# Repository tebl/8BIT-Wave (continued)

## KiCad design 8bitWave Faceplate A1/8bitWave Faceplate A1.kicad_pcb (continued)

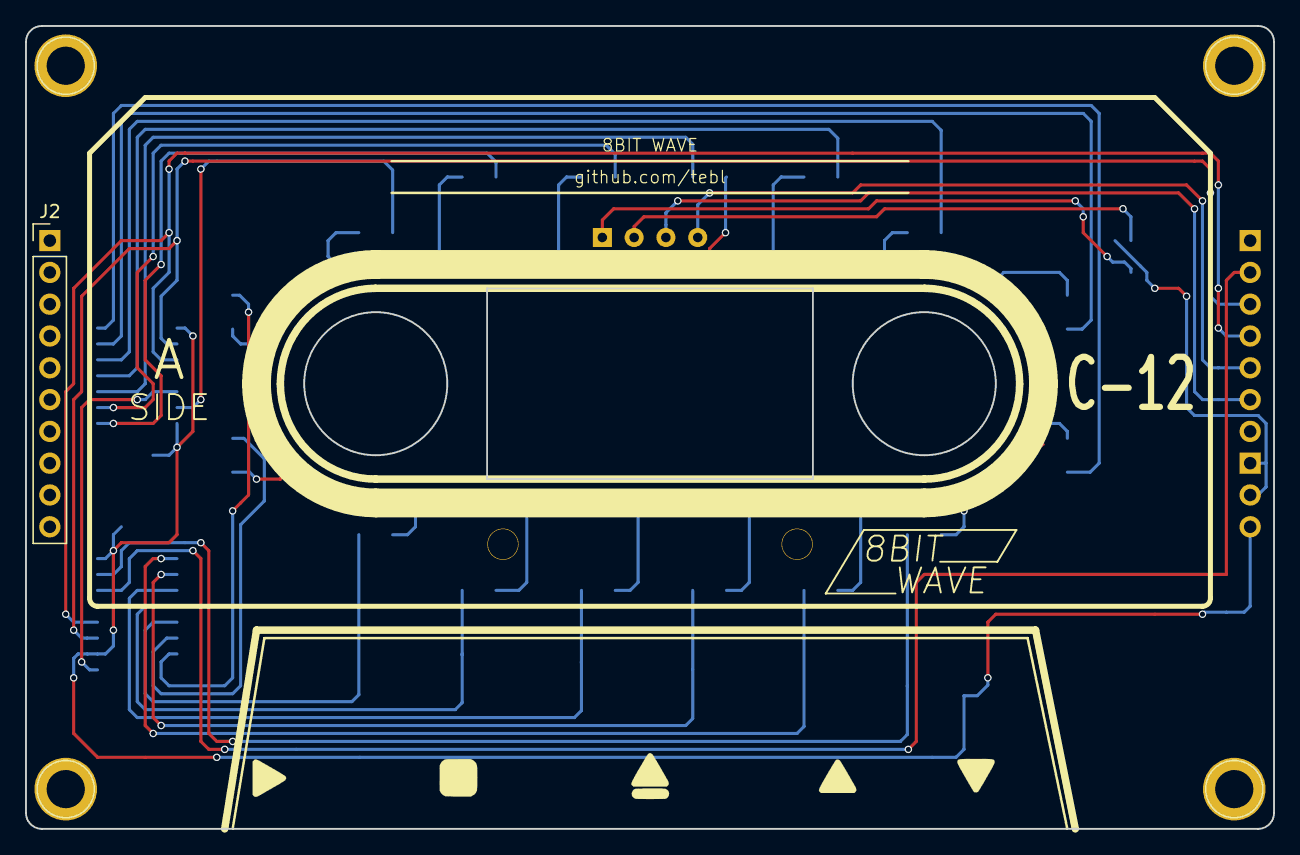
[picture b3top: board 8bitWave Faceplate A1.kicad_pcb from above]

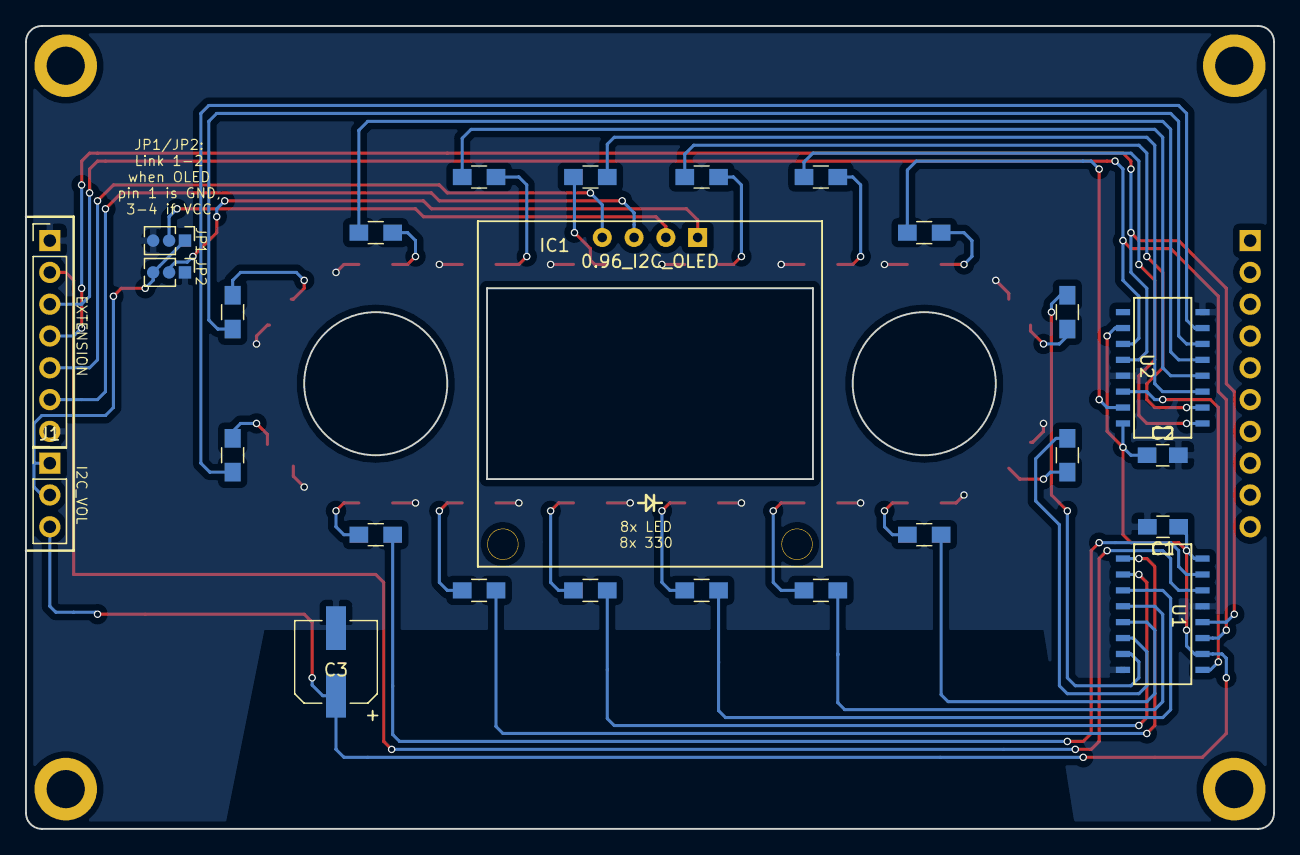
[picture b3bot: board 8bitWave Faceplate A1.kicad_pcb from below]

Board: 2 copper layers, 99.7 x 64.1 mm, 47 parts (25 on the bottom side), 43 nets.

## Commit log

2020-02-06 Schematic added
2020-02-07 Layout sketched out
2020-02-08 Tweaked silkscreen
2020-02-08 Gerber export
2020-02-08 Faceplate sketched out
2020-02-09 Faceplate tracks routed
2020-02-09 Finishing touches
2020-02-22 Hello blink LED
2020-02-22 Module updated to kicad 5
2020-02-24 Made a mess of things
2020-02-24 Build images
2020-02-24 Debounce buttons
2020-02-24 Control LEDs
2020-02-24 Display flash string helper
2020-02-24 Save some bytes of RAM
2020-02-25 Added timer to the display
2020-02-26 De-flicker OLED display
2020-02-27 Moved player details into separate file
2020-02-27 Remove file extension
2020-02-27 Fixed pause/resume
2020-02-27 Cycle user led on motor control
2020-03-02 Non-functional CAS
2020-03-03 CAS makes some noise (then crashes)
2020-03-03 Delay scrolling
2020-03-03 Updated faceplate
2020-03-03 Backplate
2020-03-04 Added README
2020-03-07 PAM8403
2020-03-20 Rotate image
2020-06-03 Play around with display code
2020-06-03 Allow faceplate to choose OLED pin order
2020-06-03 Moved bypass cap, gain jumpers
2020-06-03 Tweaked module and placement
2020-06-08 Added bypass cap
2020-06-19 Gallery images
2020-10-11 Resized gallery images
2020-12-17 Updated status
2021-01-15 Added images
2021-01-15 Renamed images
2021-01-15 Backplate README
2021-01-15 Updated images
2021-01-15 Faceplate README
2021-01-15 Added pictures
2021-01-15 Replaced picture
2021-01-15 Module README finally added
2021-01-15 Updated main README
2021-01-15 Updated faceplate A1 (KiCad 5)
2021-01-16 Added simplified faceplate A2
2021-01-16 Updated backplate (KiCad 5)
2021-01-16 Updated module (KiCad 5)
2021-01-16 Fixed some library paths
2021-01-17 Fixed PCBway links
